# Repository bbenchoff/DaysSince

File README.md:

DaysSince
=========

A 'days since' sign for the Raspberry Pi

Basically, it's two 7-segment displays for the Raspberry Pi GPIO. Add in a bit of silkscreen for a 'It has been XX days since' message, and you end up with this.

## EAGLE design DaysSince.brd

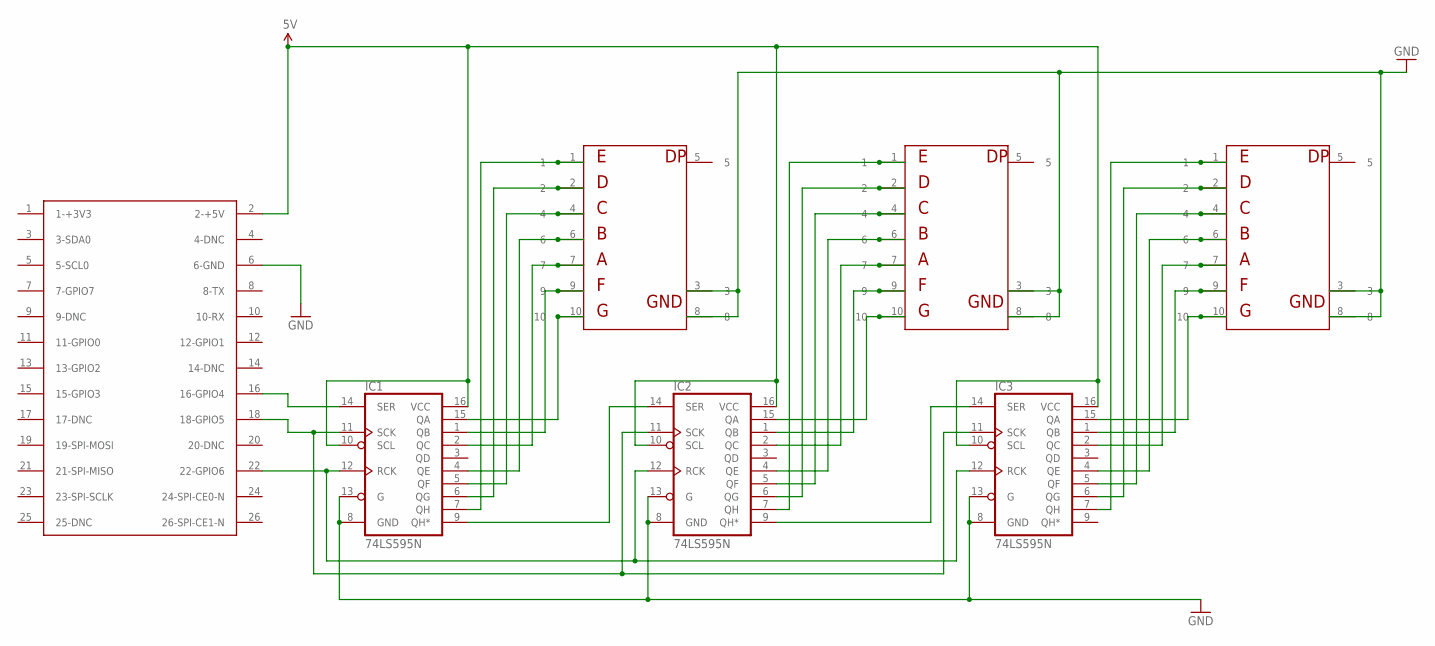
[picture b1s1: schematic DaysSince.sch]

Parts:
IC1, IC2, IC3: 74LS595N; DIL16
LED1, LED2, LED3: 7SG100012AG
U$1: RASPBERRY-PI

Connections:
5V: IC1.10 (SCL), IC1.16 (VCC), IC2.10 (SCL), IC2.16 (VCC), IC3.10 (SCL), IC3.16 (VCC), U$1.2 (2-+5V)
GND: IC1.8 (GND), IC1.13 (G), IC2.8 (GND), IC2.13 (G), IC3.8 (GND), IC3.13 (G), LED1.3, LED1.8, LED2.3, LED2.8, LED3.3, LED3.8, U$1.6 (6-GND)
unnamed: IC1.9 (QH*), IC2.14 (SER)
unnamed: IC2.9 (QH*), IC3.14 (SER)
unnamed: IC2.4 (QE), LED2.6
unnamed: IC1.12 (RCK), IC2.12 (RCK), IC3.12 (RCK), U$1.22 (22-GPIO6)
unnamed: IC1.11 (SCK), IC2.11 (SCK), IC3.11 (SCK), U$1.18 (18-GPIO5)
unnamed: IC1.14 (SER), U$1.16 (16-GPIO4)
unnamed: IC2.2 (QC), LED2.7
unnamed: IC2.1 (QB), LED2.9
unnamed: IC1.7 (QH), LED1.1
unnamed: IC1.6 (QG), LED1.2
unnamed: IC1.5 (QF), LED1.4
unnamed: IC1.4 (QE), LED1.6
unnamed: IC1.2 (QC), LED1.7
unnamed: IC1.1 (QB), LED1.9
unnamed: IC1.15 (QA), LED1.10
unnamed: IC2.7 (QH), LED2.1
unnamed: IC2.6 (QG), LED2.2
unnamed: IC2.5 (QF), LED2.4
unnamed: IC2.15 (QA), LED2.10
unnamed: IC3.7 (QH), LED3.1
unnamed: IC3.6 (QG), LED3.2
unnamed: IC3.5 (QF), LED3.4
unnamed: IC3.4 (QE), LED3.6
unnamed: IC3.2 (QC), LED3.7
unnamed: IC3.1 (QB), LED3.9
unnamed: IC3.15 (QA), LED3.10

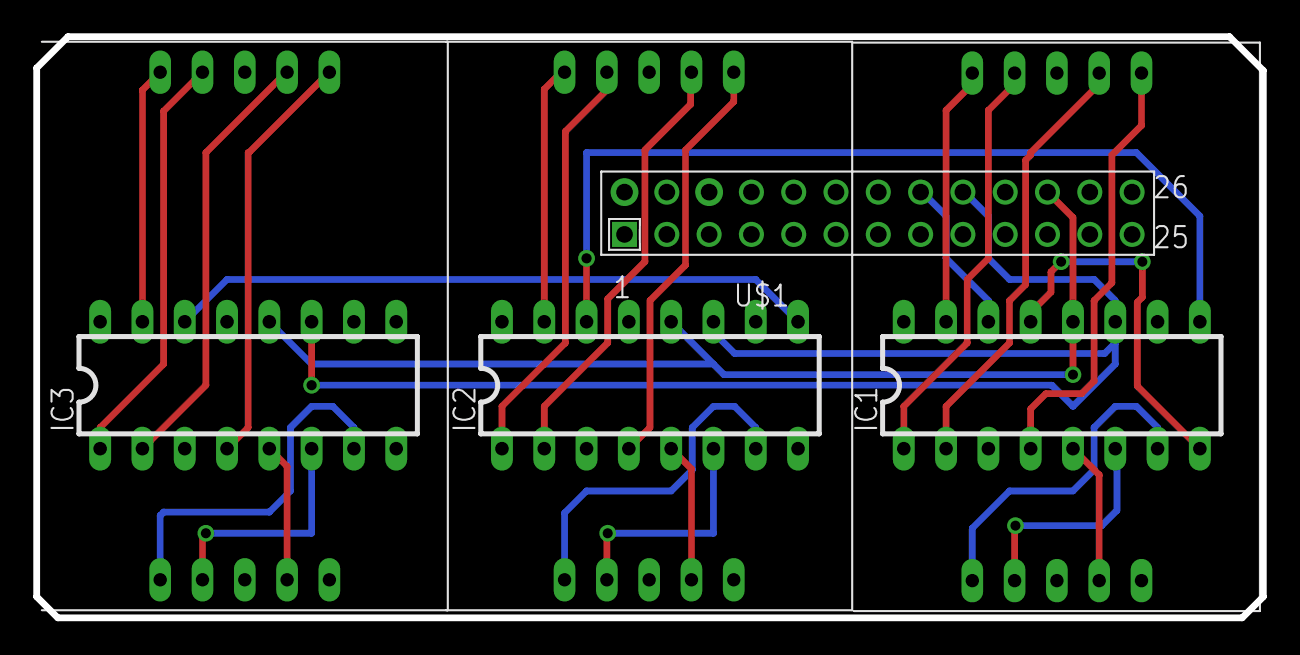
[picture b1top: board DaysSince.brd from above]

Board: 2 copper layers, 73.7 x 34.9 mm, 7 parts (0 on the bottom side), 28 nets.

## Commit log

2013-03-07 Revert "first commit"
    This reverts commit 19a7f8e67dc336aaa6501bc17e5f3c201acbdfbf.
2013-03-07 Revert "Revert "first commit""
    This reverts commit c6830731a034fff7b49a19f0bea73bb4f424d36e.
2013-03-07 First commit
    first commit of hardware. It should work, I won't know that until I get
    the boards in.
2013-03-07 Added gerbers
2013-04-11 New and improved version
    Smaller PCB, shift registers, and lower cost, woo.
2013-04-17 Updated for shift registers

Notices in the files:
parts and their libraries:
SparkFun-DigitalIC: Licensing: CC v3.0 Share-Alike You are welcome to use this library for commercial purposes.
